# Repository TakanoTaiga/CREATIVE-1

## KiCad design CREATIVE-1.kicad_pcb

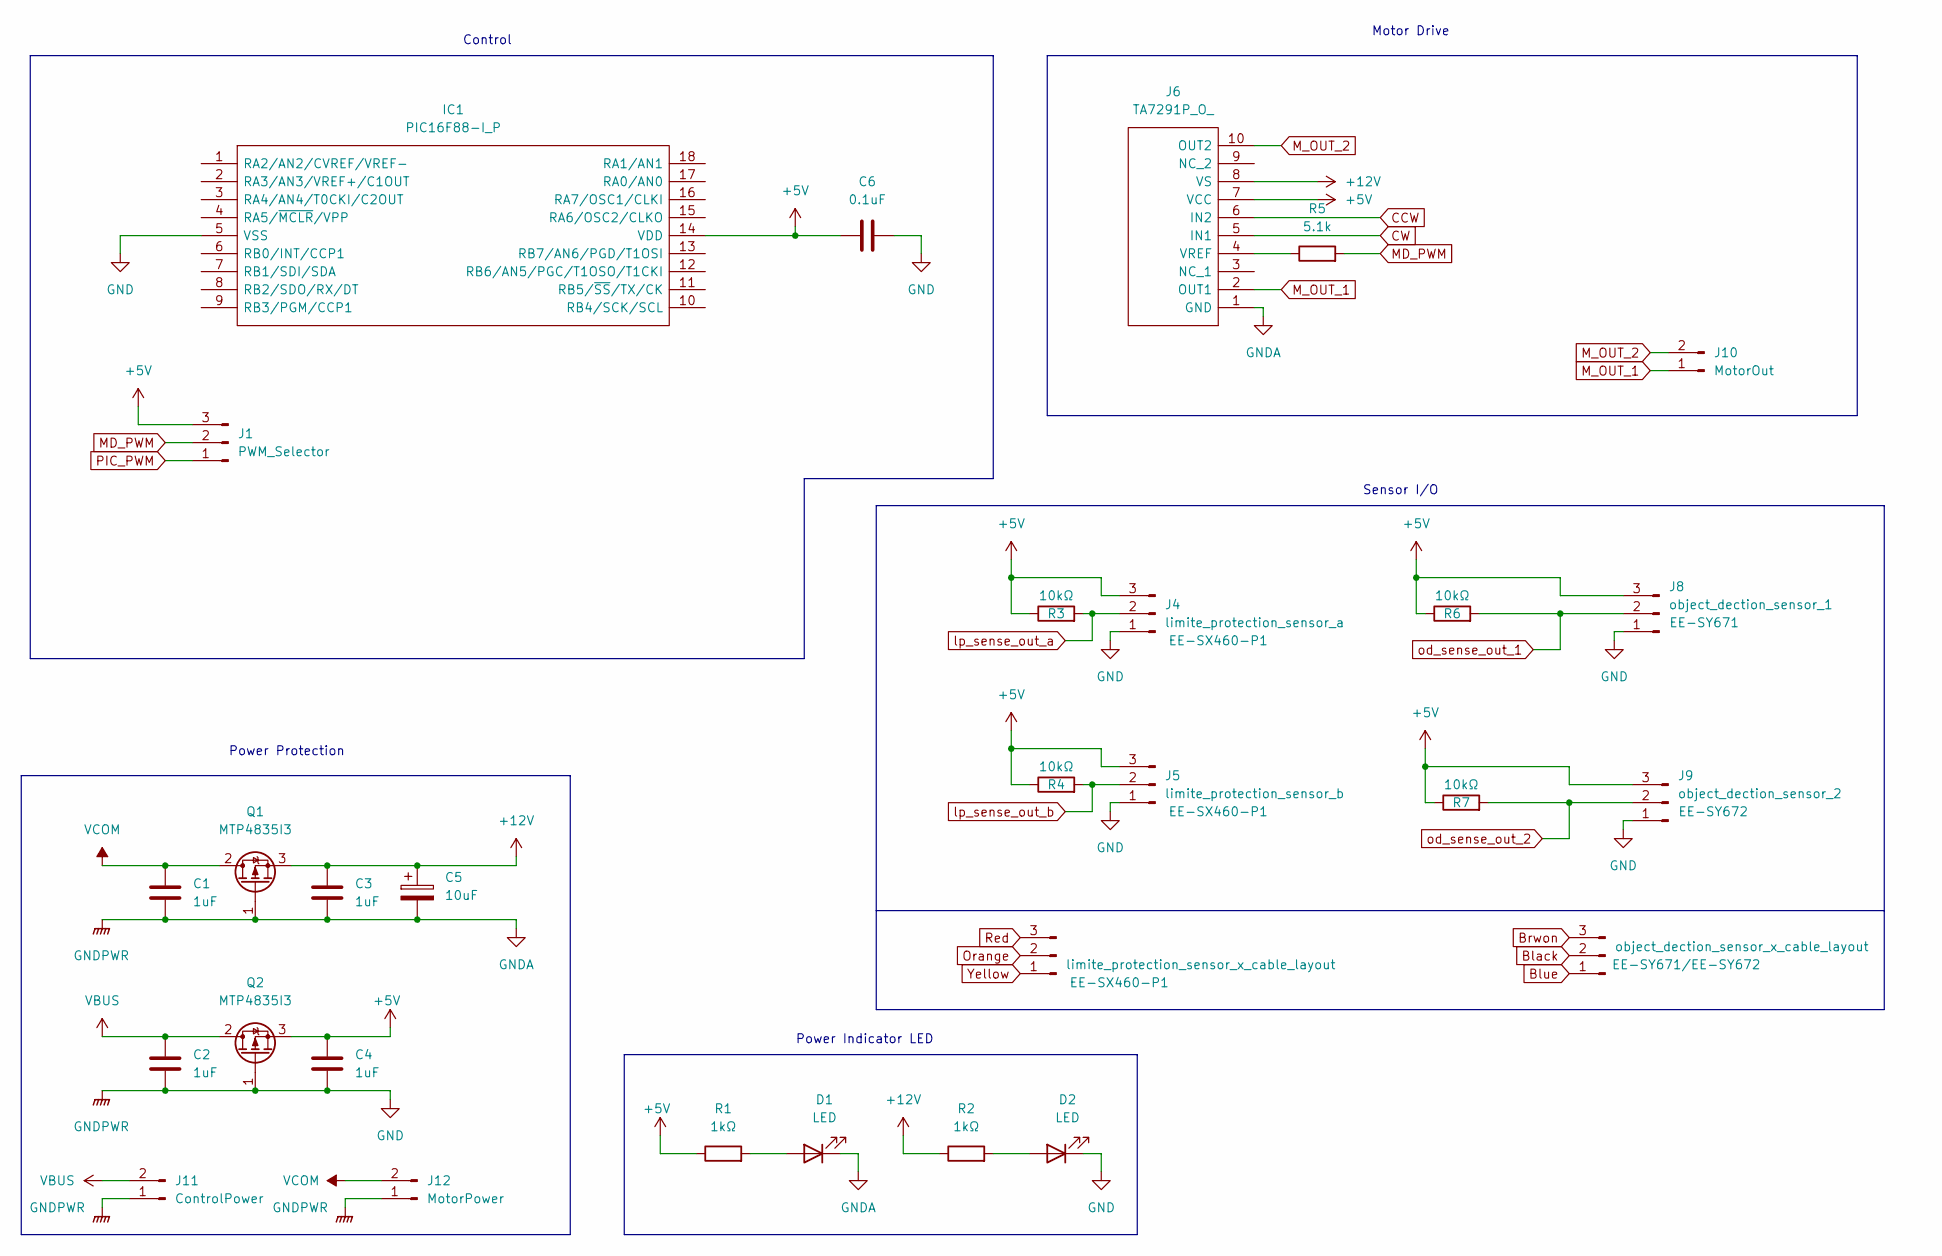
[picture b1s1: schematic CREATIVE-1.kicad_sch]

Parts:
C1, C2, C3, C4: 1uF; C_Disc_D4.3mm_W1.9mm_P5.00mm
C5: 10uF; CP_Radial_D10.0mm_P5.00mm
C6: 0.1uF; C_Disc_D4.3mm_W1.9mm_P5.00mm
D1, D2: LED; LED_D3.0mm
IC1: PIC16F88-I_P; DIP794W56P254L2286H533Q18N; Manufacturer_Part_Number PIC16F88-I/P
J1: PWM_Selector; PinHeader_1x03_P2.54mm_Vertical
J3: limite_protection_sensor_x_cable_layout; PinHeader_1x03_P2.54mm_Vertical
J4: limite_protection_sensor_a; PinHeader_1x03_P2.54mm_Vertical
J5: limite_protection_sensor_b; PinHeader_1x03_P2.54mm_Vertical
J6: TA7291P_O_; TO254P420X2700X1580-10P; Manufacturer_Part_Number TA7291P(O)
J7: object_dection_sensor_x_cable_layout
J8: object_dection_sensor_1; PinHeader_1x03_P2.54mm_Vertical
J9: object_dection_sensor_2; PinHeader_1x03_P2.54mm_Vertical
J10: MotorOut; TerminalBlock_bornier-2_P5.08mm
J11: ControlPower; TerminalBlock_bornier-2_P5.08mm
J12: MotorPower; TerminalBlock_bornier-2_P5.08mm
Q1, Q2: MTP4835I3; PinHeader_1x03_P2.54mm_Vertical
R1, R2: 1kΩ; R_Axial_DIN0204_L3.6mm_D1.6mm_P2.54mm_Vertical
R3, R4, R6, R7: 10kΩ; R_Axial_DIN0204_L3.6mm_D1.6mm_P2.54mm_Vertical
R5: 5.1k; R_Axial_DIN0204_L3.6mm_D1.6mm_P2.54mm_Vertical

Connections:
+5V: C4.1, C6.1, IC1.14 (VDD), J1.3, J4.3, J5.3, J6.7 (VCC), J8.3, J9.3, Q2.3 (S), R1.1, R3.1, R4.1, R6.1, R7.1
+12V: C3.1, C5.1, J6.8 (VS), Q1.3 (S), R2.1
CCW: J6.6 (IN2)
CW: J6.5 (IN1)
GND: C1.2, C2.2, C3.2, C4.2, C5.2, C6.2, D1.1 (K), D2.1 (K), IC1.5 (VSS), J4.1, J5.1, J6.1 (GND), J8.1, J9.1, J11.1, J12.1, Q1.1 (G), Q2.1 (G)
MD_PWM: J1.2, R5.2
M_OUT_1: J6.2 (OUT1), J10.1
M_OUT_2: J6.10 (OUT2), J10.2
unnamed: D1.2 (A), R1.2
unnamed: D2.2 (A), R2.2
unnamed: J6.4 (VREF), R5.1
PIC_PWM: J1.1
VBUS: C2.1, J11.2, Q2.2 (D)
VCOM: C1.1, J12.2, Q1.2 (D)
lp_sense_out_a: J4.2, R3.2
lp_sense_out_b: J5.2, R4.2
od_sense_out_1: J8.2, R6.2
od_sense_out_2: J9.2, R7.2

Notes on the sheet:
Power Indicator LED
Control
Power Protection
Motor Drive
Sensor I/O

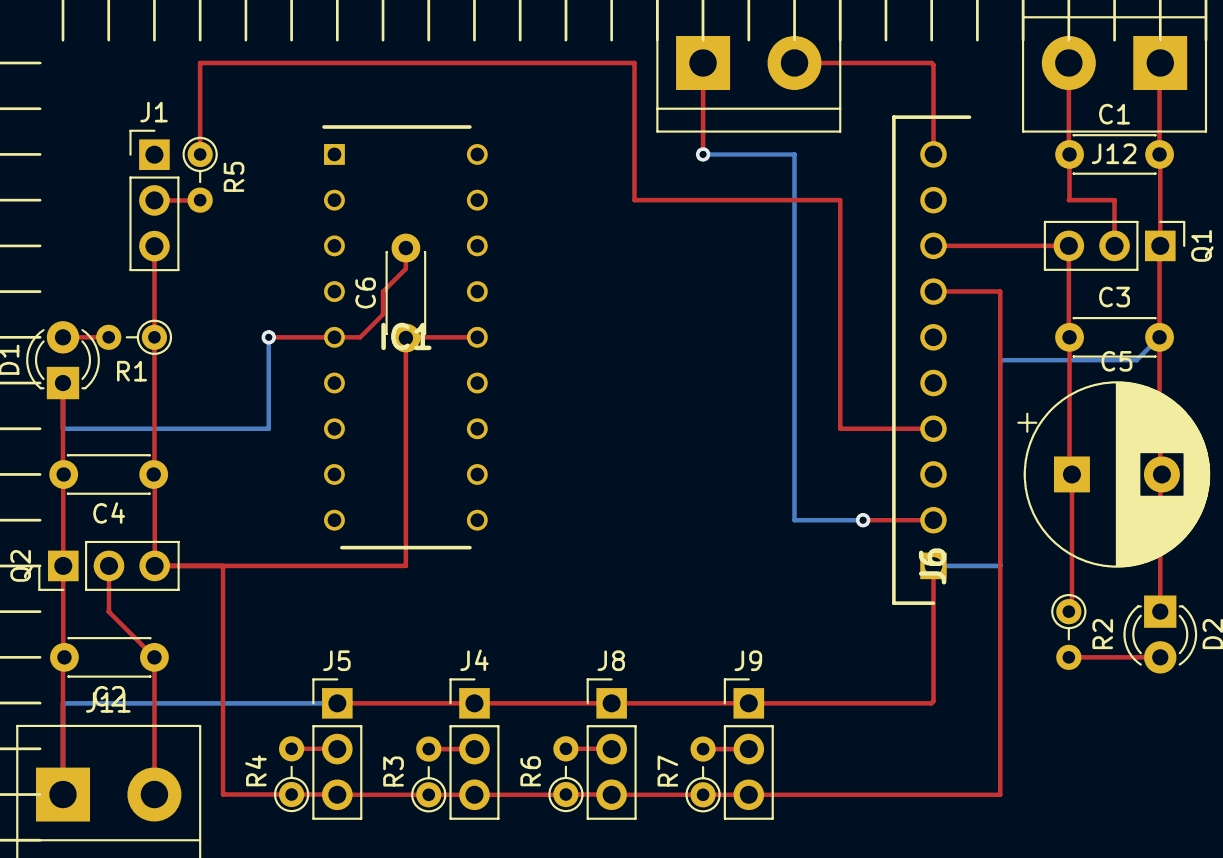
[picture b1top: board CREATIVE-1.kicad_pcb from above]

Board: 2 copper layers, 27 parts (0 on the bottom side), 15 nets.

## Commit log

2023-01-03 Fix a few bugs

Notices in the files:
CREATIVE-1.kicad_sch:
Copyright © 2022 Taiga Takano. All rights reserved.
